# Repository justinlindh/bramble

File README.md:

<h1 align="center">Bramble</h1>

<p align="center">
  Privacy-first LoRa mesh networking for ESP32-S3, built with ESP-IDF.
</p>

<p align="center">

</p>

Bramble is an encrypted, multi-hop mesh protocol and firmware stack for long-range, infrastructure-free communication. It is designed for resilient field use while reducing metadata exposure; [docs/SECURITY-MODEL.md](docs/SECURITY-MODEL.md) documents exactly what is and is not protected.

## Table of Contents

- [What is Bramble?](#what-is-bramble)
- [What Makes Bramble Different](#what-makes-bramble-different)
- [Web Client](#web-client)
- [Hardware Targets](#hardware-targets)
- [Simulator](#simulator)
- [Emulator](#emulator)
- [Getting Started](#getting-started)
- [Testing](#testing)
- [Architecture](#architecture)
- [Documentation](#documentation)
- [API and SDK](#api-and-sdk)
- [CI/CD](#cicd)
- [Status](#status)
- [Contributing and Community](#contributing-and-community)
- [License](#license)

## What is Bramble?

Bramble is a secure LoRa mesh protocol and firmware implementation for ESP32-S3 devices with SX1262 radios. It focuses on practical private communications in constrained, lossy RF environments, with explicit handling for routing, retransmission, airtime limits, and node identity.

The firmware runs on real hardware (including T-Deck Plus and Heltec V3/V4 targets), with host-side testing used to validate protocol behavior continuously during development.

## What Makes Bramble Different

Compared to Meshtastic and MeshCore-style systems, Bramble leans on privacy and on authenticated, confirmable delivery at the protocol level. It is an early project: functional and hardware-verified on a small bench mesh, but not yet field-tested at scale. The claims below are what the code on `main` does, with the honest limits stated alongside.

- **Dual-substrate routing.** Two forwarding substrates ship, and a runtime toggle (`s_flood_transport`, default off) selects between them. **Reactive AODV is the default:** RREQ/RREP discovery, a cached route table, reverse-route breadcrumbs learned from DATA, intermediate-node RREP, and route-forwarded ACKs. DM airtime is `O(path_length)`, not `O(N)`. **Flooding is the opt-in alternative:** hop-limited (configurable, default 8, range 1..32), deduplicated, airtime-budget-gated unicast/channel floods with a flooded ACK for route-free sender confirmation. Both substrates are first-class; the toggle picks one.
- **Authenticated traffic (wire v4), no insecure bootstrap.** DATA frames and the control plane (RREP, RERR, ACK, delivery receipt, beacon) carry a network-key HMAC that relays verify before acting; a captured frame cannot be forged or replayed by an outsider on a provisioned network. There is no public default key: an unprovisioned node is inert (fail-closed) and refuses to emit or accept any authenticated frame until a real per-fleet key is provisioned (minted on-device or pasted in). Residual: any network-key holder is an insider and can still forge these MACs, narrowed by per-node identity rather than by provisioning ([docs/SECURITY-MODEL.md](docs/SECURITY-MODEL.md)).
- **Confirmed delivery.** Acknowledged tiers report DELIVERED vs FAILED to the sender rather than fire-and-forget. Honest envelope: reactive holds confirmed delivery at small, dense scale; the flooded confirmation holds at low-to-moderate message load and **degrades at high load** because flood airtime scales as `O(messages x nodes)`. It is explicitly not a high-load guarantee.
- **End-to-end direct messages.** DMs use per-peer AES-256-GCM sessions keyed by a role-symmetric quad-DH X25519 exchange (`components/dm_session`), and are not readable by other channel members. Each message has forward secrecy from a symmetric HKDF ratchet, with a coarse per-epoch DH ratchet for post-compromise recovery. An identity-bound 7-digit safety number (SAS) lets two people verify a contact out of band; the verification UX ships in the web client, the T-Deck graphical build, and on the e-paper pager itself (a per-peer view under the Nodes screen with a two-step confirm), and verified state is remembered per contact and cleared automatically if a contact's identity key changes. See [docs/SECURITY-MODEL.md](docs/SECURITY-MODEL.md) for the threat model and residuals.
- **Channel encryption + multi-hop channels.** Channel messages use AES-256-GCM (AEAD) with the channel ID hidden inside the ciphertext, and they relay multi-hop via the flood relay.
- **Privacy-first routing.** Route-request sources are pseudonymized per query, so forwarded route requests do not carry the originator's address.
- **Airtime budgeting:** every transmission goes through one budget-gated TX path (`components/radio/tx_gate.c`) with real time-on-air costing, per-tier token buckets, and regional duty-cycle caps enforced where the frequency plan requires them (for example EU 868 at 1%).
- **3-tier reliability model:** Broadcast (fire-and-forget), Normal (acknowledged, 3 retries with backoff), and Critical (8 retries plus delivery receipts carrying the relay path).
- **Cryptographic node identity + optional fleet trust anchor.** Each node has an Ed25519 identity whose 4-byte address is the hash of its own public key (`SHA-256(ed25519_pub)[0:4]`), so an address cannot be claimed without the matching key: address impersonation is a preimage search, not a TOFU race. Nodes flood self-signed identity attestations that peers verify and TOFU-pin, refusing and counting any later conflicting key for a pinned address. An optional per-fleet trust anchor (an operator-held Ed25519 key that endorses each member's identity with a cert) closes Sybil identity minting on an anchored mesh, because an anchored node only pins peers carrying a cert its anchor signed. Residuals stated in the same breath: a compromised endorsed insider stays a valid member (endorsement is admission control, not behavioral trust), the anchor seed is the fleet's trust root and its custody is the whole scheme, and an un-anchored mesh keeps unforgeable but free-to-mint identities ([docs/trust-anchor.md](docs/trust-anchor.md), [docs/SECURITY-MODEL.md](docs/SECURITY-MODEL.md)).
- **Attested roll-call.** An initiator broadcasts a roll-call and every member answers with an Ed25519 identity-signed unicast, building a per-member ledger with relay paths (`bramble.startRollCall` / `bramble.getRollCall`, with a panel in the web client). An anchored mesh audits against the endorsed member set; an un-anchored mesh reports observed responders only. A signature proves an answer and absence proves nothing; both initiation and answering are rate-limited because a roll-call costs N unicast answers. Verified by host tests and the collision-modeled simulator; no field deployment ([docs/rollcall.md](docs/rollcall.md)).
- **Deployment digital twin.** Each node exports its observed topology over RPC (`bramble.exportTopology`), and the simulator's `twin` subcommand replays that deployment against the collision model: capacity (delivery rate vs offered load) and which single node's loss partitions the mesh. The twin replays observed links at a moment in time; it predicts nothing about unplaced nodes, and its results are simulation ([docs/digital-twin.md](docs/digital-twin.md)).
- **Browser playground.** `make playground` boots the actual firmware binary as a small virtual fleet on a simulated ether, with a guided tour through provisioning (including the fail-closed inert state), multi-hop relay, SAS verification, and a delivery receipt. First contact needs no hardware and no toolchain; a browser fleet is not a field deployment ([docs/playground.md](docs/playground.md)).
- **Store-and-forward mailbox:** offline nodes receive queued messages when they rejoin the mesh.
- **Location sharing with privacy tiers:** presence, zone (a 0.003° by 0.006° cell, about 334 m north-south and 668 m east-west at the equator), or exact; per-peer control over what you share and with whom. Location payloads are AES-256-GCM encrypted end to end and padded to a fixed size so the ciphertext does not leak which tier was chosen; timing and the fact that a node shares location remain observable ([docs/SECURITY-MODEL.md](docs/SECURITY-MODEL.md)).
- **Browser-based flashing:** flash firmware to new devices directly from the web, no toolchain required.

For a deeper feature-by-feature analysis, see [docs/COMPARISON.md](docs/COMPARISON.md).

## Web Client

Bramble includes a web client for live network operation and monitoring. It provides real-time chat (including delivery badges), map-based peer location views, neighbor and route visualization, traffic monitoring, channel management, and radio configuration.

See [docs/webapp/chat.md](docs/webapp/chat.md) for current web client behavior and usage notes. To run it from source, `cd webapp && npm ci && npm run dev`; [webapp/README.md](webapp/README.md) covers the dev workflow, the WiFi-transport backend, and the Electron builds.

A desktop app (Linux, Windows, macOS) is also available, built from the same webapp. It connects directly to nodes on your local network instead of going through a hosted proxy, and can discover nodes on the LAN automatically. See [docs/webapp/desktop.md](docs/webapp/desktop.md).

## Hardware Targets

| Board | MCU | Display | Input | Radio | Audio | Status |
| ------ | ----- | --------- | ------- | ------- | ------- | -------- |
| Heltec WiFi LoRa 32 V3 | ESP32-S3 | 0.96" SSD1306 OLED (128x64) | Buttons | SX1262 | N/A | Running target |
| Heltec WiFi LoRa 32 V4 | ESP32-S3 | OLED + optional L76K GNSS | Buttons | SX1262 | N/A | Running target |
| LilyGo T-Deck Plus | ESP32-S3 | ST7789 320x240 LCD with LVGL v9 UI | GT911 capacitive touch + I2C keyboard | SX1262 with TCXO (DIO3 1.8V, DC-DC) | I2S with NVS-persisted volume | Running target with full GUI |
| Bramble Pager v1 (custom PCB) | ESP32-S3-WROOM-1 | 2.13" GDEY0213B74 e-paper (SSD1680, 250x122) | Buttons | SX1262 with TCXO and DIO2 RF switch (DC-DC) | Buzzer + vibra alerts | Design complete, boards not yet ordered |
| Seeed Wio-WM1110 Dev Kit | nRF52840 | None (BLE-only interface) | None | LR1110 | N/A | Experimental: joins the bench mesh, BLE RPC + provisioning over an encrypted link, identity/key/bonds persist in flash; GNSS and power management not yet implemented ([nrf/](nrf/)) |
| Seeed SenseCAP T1000-E (card tracker) | nRF52840 | None (BLE-only interface) | Button | LR1110 | Buzzer | Experimental: boots, BLE RPC, joins the mesh; GNSS driver implemented for the onboard AG3335 module and bench-verified (2026-07-31); power management not yet implemented ([nrf/](nrf/)) |

The Bramble Pager v1 is a custom in-house board, not an off-the-shelf dev kit: its own 96x50mm 2-layer PCB (ESP32-S3-WROOM-1 + SX1262 with a DIO2 RF switch, GDEY0213B74 2.13" e-paper, ATGM336H GPS, buzzer, vibration motor, and status LED), JLCPCB-fabbable, in a 3D-printed case. The authoritative design tree (spec, schematic, PCB, BOM, case, and bring-up gates) is [hardware/pager/v1/](hardware/pager/v1/); build it with the `bramble-pager` board profile.

This is what the firmware paints on each display class, as real framebuffers (T-Deck captured on hardware, the others rendered by the real firmware in the emulator):

<table>
<tr>
<td align="center" width="34%"></td>
<td align="center" width="33%"></td>
<td align="center" width="33%"></td>
</tr>
<tr>
<td align="center"><b>T-Deck Plus</b>: LVGL color UI</td>
<td align="center"><b>Heltec OLED</b>: text UI</td>
<td align="center"><b>Pager v1</b> (alpha): e-paper text UI</td>
</tr>
</table>

Each image links to its device's section in the [device screen gallery](docs/device-screens.md), which shows every screen and documents how each capture was made.

## Simulator

Bramble ships with a mesh simulator that runs real protocol code against a virtual radio layer and renders topology/traffic in a browser. The radio layer models the shared LoRa medium (real time-on-air, collisions, capture, half-duplex, listen-before-talk), making it the primary proving ground for scale and routing behavior before field deployment.

See [simulator/README.md](simulator/README.md) for setup and scenarios. For measured scale results under the collision model, [docs/results/simulation-2026-07-honest-baseline.md](docs/results/simulation-2026-07-honest-baseline.md) is the source of truth (it supersedes the June numbers for planning; the earlier collision-free "100% at 200 nodes" figures were retracted as sim artifacts). In short, re-measured on 2026-07-24 at the PHY firmware actually transmits on (the frequency plan's SF9/125 kHz, not the radio profile's SF10): 30% message delivery at 10 nodes, 10% at 50, 0-5% at 100 and 0% at 200, as a single channel saturates under control-plane load (0.91 erlang offered by control traffic alone at 50 nodes, 1.94 at 200). Scale is bounded by radio profile, node density, and hop budget; there is no field-tested-at-scale result.

## Emulator

The simulator drives real protocol code through a test harness; the emulator goes one step further and runs the **actual firmware binary**. Each virtual node is `app_main` compiled for ESP-IDF's linux target, booted with a virtual board profile, with the radio, e-paper display, buttons, GPS, and battery replaced by virtual drivers at the existing hardware seams. N virtual Bramble Pagers attach to the gosim ether and are rendered in a browser as the physical device: a faithful SSD1680 e-paper panel, clickable buttons, per-node consoles, and true per-node identities that survive restart. It is the packaging/UX proving ground the simulator is not: what a user actually sees and does on the device.

Quick start: `cd emulator && make run` (local toolchain) or `docker compose up --build` (zero prerequisites), then open the printed URL and load the `emu-channel-delivery` scenario. A gated PHY-passthrough bridge lets a serial-attached real node inject the physical RF channel into the virtual ether. See [emulator/README.md](emulator/README.md) for setup, scenarios, and the headless CI/E2E suites. A QEMU true-VM backend (running the exact flashable image) is a documented phase-2 follow-on, not yet built.

## Getting Started

Full build/flash instructions (including board-specific profiles and USB-port notes) are in [docs/BUILDING.md](docs/BUILDING.md).

Quick start (building from source needs ESP-IDF v5.4.1; see
[docs/BUILDING.md](docs/BUILDING.md) to install and activate it):

```bash
git clone https://github.com/justinlindh/bramble.git
cd bramble

# activate ESP-IDF in this shell first
source "$IDF_PATH/export.sh"

bash scripts/flash.sh local heltec-v3 build
bash scripts/flash.sh local heltec-v3 flash /dev/ttyUSB0
```

Use `tdeck-plus` instead of `heltec-v3` for T-Deck Plus builds.

No toolchain, no problem: the [web flasher](https://bramblemesh.org/web-flasher/)
flashes a device over USB straight from the browser. If a build or flash
stalls (serial permissions, a missing toolchain, a port collision), see
[docs/troubleshooting.md](docs/troubleshooting.md).

**Keeping it up to date.** Once a node is on your WiFi it installs new firmware over the air from the web client, no cable and no toolchain: [docs/updating-your-node.md](docs/updating-your-node.md).

**First-time setup.** A freshly flashed node boots unprovisioned and inert: it has no network key, so it will not mesh (it neither emits nor accepts authenticated control-plane traffic) until you provision one, and the web client shows a prominent UNPROVISIONED banner until then. Follow [docs/getting-started.md](docs/getting-started.md) to connect the web client, provision a network key, optionally enroll the node under a trust anchor, and send your first message.

## Testing

Host-side tests cover crypto, routing, security, packet handling, reliability, and integration behavior.

```bash
cd test
./run_all_tests.sh
```

## Architecture

Bramble is organized as ESP-IDF components with clear boundaries between protocol logic, radio abstraction, security, reliability, and UI/control layers. The architecture is designed so core protocol behavior can be validated on host and simulator environments before device rollout.

For the full component breakdown and interaction diagrams, see [docs/bramble-architecture.md](docs/bramble-architecture.md).

## Documentation

- [docs/README.md](docs/README.md): documentation index (recommended entry point)
- [CONTRIBUTING.md](CONTRIBUTING.md): contributor setup, quality gates, and conventions
- [docs/troubleshooting.md](docs/troubleshooting.md): common build, flash, and test stalls
- [docs/BUILDING.md](docs/BUILDING.md): build, flash, monitor workflows
- [docs/bramble-architecture.md](docs/bramble-architecture.md): component-level architecture
- [docs/SECURITY-MODEL.md](docs/SECURITY-MODEL.md): threat model, verified protections, and known gaps
- [docs/auth.md](docs/auth.md): RPC authentication (on by default), pairing, and the browser origin allowlist
- [docs/COMPARISON.md](docs/COMPARISON.md): comparison with other mesh systems
- [docs/bramble-protocol-spec.md](docs/bramble-protocol-spec.md): protocol details
- [docs/bramble-testing.md](docs/bramble-testing.md): test strategy and coverage
- [docs/updating-your-node.md](docs/updating-your-node.md): update your node over the air from the web client
- [docs/ota-rollout.md](docs/ota-rollout.md): OTA operator workflow (RPC recipes, dev-build loop)
- [docs/quality-policy.md](docs/quality-policy.md): repo-wide CI gates, promotion criteria, and rollback levers
- [docs/quality-policy-webapp.md](docs/quality-policy-webapp.md): webapp workflow required/advisory mapping, local parity commands, and rollback levers
- [simulator/README.md](simulator/README.md): simulator usage
- [docs/webapp/chat.md](docs/webapp/chat.md): web client chat and UX notes

## API and SDK

Bramble exposes a JSON-RPC 2.0 interface for device control and observability.

- [api/openapi.yaml](api/openapi.yaml): OpenAPI spec for the RPC surface (synced to the firmware registry, CI-enforced by `scripts/check-rpc-contract.sh`; see [VERSIONING.md](VERSIONING.md))
- [bramble-go](https://github.com/justinlindh/bramble-go): Go SDK (serial, WebSocket, BLE)
- [bramble-cli](https://github.com/justinlindh/bramble-cli): CLI/TUI built on bramble-go
- [VERSIONING.md](VERSIONING.md): compatibility matrix

## CI/CD

- [.github/workflows/quality.yml](.github/workflows/quality.yml) runs the umbrella required gates: host tests, static checks, gosim integration, webapp checks, web-flasher tests, and the emulator suite.
- [.github/workflows/firmware-quality.yml](.github/workflows/firmware-quality.yml) runs firmware quality gates: required clang-format/shellcheck/actionlint.
- [.github/workflows/webapp-quality.yml](.github/workflows/webapp-quality.yml) runs webapp required gates (lint/typecheck/unit/build/e2e smoke).
- [.github/workflows/release-components.yml](.github/workflows/release-components.yml) publishes per-component releases and attaches firmware factory images and desktop installers.
- Additional workflow definitions live in [.github/workflows](.github/workflows).

## Status

Bramble is an early but fully functional project: the protocol stack is implemented end to end, reviewed and host-tested, and running stable on real hardware (T-Deck Plus, Heltec V3, and Heltec V4). Every change must pass the full host test suite as a required CI gate (`test/run_all_tests.sh`, which fails if any suite fails or none are found). It has not yet been field-tested at scale, and development is ongoing.

## Contributing and Community

Contributions are welcome, and you do not need hardware to make one. The
webapp, the simulator, the host test suites, and the docs all build and run on
an ordinary machine.

- **[CONTRIBUTING.md](CONTRIBUTING.md)**: setup, the quality gates, branch and
  commit conventions, and what a good pull request looks like. Start there.
  Note the one step that is easy to miss: run `make setup-hooks` once per
  clone so the pre-commit checks run on your machine instead of failing in CI.
- **[docs/troubleshooting.md](docs/troubleshooting.md)**: serial permissions,
  toolchain targets, port collisions, and the other common first-run stalls.
- **[Issues](https://github.com/justinlindh/bramble/issues)**: bug reports and
  feature requests.
- **[Discussions](https://github.com/justinlindh/bramble/discussions)**:
  questions, ideas, and show-and-tell.
- **[SECURITY.md](SECURITY.md)**: how to report a vulnerability privately.
  Please do not open a public issue for one.
- **[CODE_OF_CONDUCT.md](CODE_OF_CONDUCT.md)**: what is expected of everyone
  taking part.

GitHub is canonical for outside contributions. Any other remote you may come
across is a mirror.

## License

MIT; see [LICENSE](LICENSE)

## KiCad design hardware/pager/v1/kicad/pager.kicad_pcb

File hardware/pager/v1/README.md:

# Bramble Pager v1

A full Bramble mesh node (TX-capable; the mesh has no receive-only role) built into a
90s-pager formfactor: always-readable 2.13" e-paper, 1S LiPo with USB-C charge and
load-share, magnetic buzzer plus coin vibration motor, and a 3D-printed enclosure. It
runs stock Bramble firmware as a new board target (`bramble_pager`) that reuses every
Heltec-V3 pin assignment legal on an ESP32-S3-WROOM-1, adds an SSD1680 e-paper display,
and carries an ATGM336H GNSS receiver. Board is ~96x50mm landscape, 2-layer 1.6mm,
built for JLCPCB economic PCBA. This directory is the source of truth for the design.

**Status:** design complete and merged to `main` (schematic, PCB, BOM, and enclosure done;
firmware board profile `main/boards/bramble_pager.h` landed). Boards are **not yet ordered**:
the pre-fab gates in [`ERRATA.md`](ERRATA.md) (FPC 1:1 fold mockup, bench-verified 0x9D
DIO2 RF-switch flag, final DRC 0/0/0) must close first. See
[the archived pre-fab review](../../../docs/archive/plans/pager-v1-review-2026-07-10.md)
for the independent pre-fab review and [`SOURCING.md`](SOURCING.md) for the hand-purchased
(non-JLCPCB) parts. Production outputs (gerbers, BOM, positions) are under
[`kicad/production/`](kicad/production/).

The full requirement set, pin map, block-by-block rationale, and firmware deltas live in
`DESIGN.md`. This README covers the workflow: where truth lives, how to validate, what
must never regress, and how to bring a first article up.

## Sources of truth (ranked)

When two artefacts disagree, the higher entry wins. Never argue with ERC or DRC; fix the
schematic or the doc.

| Rank | Artefact | Authority |
| --- | --- | --- |
| 1 | `kicad/*.kicad_sch` | Canonical electrical netlist. If a doc says a pin is wired to X and the schematic says Y, the schematic is correct. |
| 2 | `kicad/pager.kicad_pcb` | Canonical physical placement and routing. Authoritative for positions, layers, copper geometry. |
| 3 | `DESIGN.md` | Requirements, pin map, block rationale, do-not-regress invariants. |
| 4 | `COMPONENTS.md` | Per-component catalogue: value, package, LCSC part, nets, purpose, datasheet pinout citation. |
| 5 | `NET_TOPOLOGY.md` | Net-by-net prose for the nets that matter: why each exists, how each block is wired. |

`COMPONENTS.md` and `NET_TOPOLOGY.md` are derived docs. They mirror the schematic; if
either disagrees with a `.kicad_sch`, the schematic is right and the doc is a bug.

## File map

```text
hardware/pager/v1/
├── README.md            # this file
├── DESIGN.md            # authoritative spec: requirements, pin map, blocks, invariants
├── COMPONENTS.md        # per-component catalogue (derived)
├── NET_TOPOLOGY.md      # net-by-net wiring prose (derived)
├── ERRATA.md            # errata + pre-fab open items
├── SOURCING.md          # hand-purchased (non-JLCPCB) parts + live sources
├── mockup-fpc-1to1.pdf  # 1:1 FPC fold mockup (print gate before ordering)
├── case/                # OpenSCAD enclosure + exported STLs
└── kicad/
    ├── pager.kicad_pro  # KiCad project
    ├── pager.kicad_sch  # root sheet (hierarchical references only)
    ├── power.kicad_sch  # USB-C, charger, protection, load-share, LDO
    ├── radio.kicad_sch  # LoRa module, GNSS module, both RF feeds
    ├── epaper.kicad_sch # display connector + boost / charge-pump
    ├── mcu.kicad_sch    # ESP32-S3, buttons, buzzer, vibra, LED, I2C header
    ├── pager.kicad_pcb  # PCB layout
    ├── pager.kicad_dru  # hard DRC backstops (RF, power-rail widths)
    ├── production/      # fabrication outputs: gerbers, bom.csv, positions
    └── easyeda/         # imported footprints/symbols (dimension-verified)
```

The original implementation plan and the independent pre-fab review are historical
process artifacts and live under [`docs/archive/plans/`](../../../docs/archive/plans/):
[`pager-v1-plan.md`](../../../docs/archive/plans/pager-v1-plan.md) and
[`pager-v1-review-2026-07-10.md`](../../../docs/archive/plans/pager-v1-review-2026-07-10.md).

## Validation gates

Both gates use `kicad-cli` (not the KiCad MCP). MCP ERC/DRC read stale in-memory state
and have missed real violations; they are never authoritative here.

### Schematic ERC

```bash
kicad-cli sch erc --severity-error --exit-code-violations \
  hardware/pager/v1/kicad/pager.kicad_sch -o /tmp/erc.rpt
```

Must exit 0 (zero errors). The committed `kicad/pager-erc.rpt` is the last clean run.

### PCB DRC

```bash
kicad-cli pcb drc --refill-zones \
  hardware/pager/v1/kicad/pager.kicad_pcb -o /tmp/drc.rpt
```

Must report 0 unconnected, 0 clearance, 0 dangling. `--refill-zones` is mandatory;
without it DRC reads stale zone fills and misses zone-island and same-layer clearance
violations. The `.kicad_dru` net-name patterns must be re-audited against the actual
hierarchical net names (`/sheet/NET`) before every fab; a pattern that silently voids
against a renamed net gives a false-clean pass (the Digits v2 SW_NODE lesson).

## Do-not-regress invariants

Copied from `DESIGN.md`. Regressing any of these is a production defect.

- Every non-stdlib pinout and every pin-numbering orientation must be verified against
  the manufacturer datasheet (page/figure cited in `COMPONENTS.md`). EasyEDA part data,
  vendor symbol drawings, and "it is usually like this" do NOT count as verification.
  Claims that could not be datasheet-confirmed are tracked as open risks, not assumed.
- CC1 and CC2 each get their own 5.1k, never shared.
- Battery sense divider taps BAT+ (cell side), not VSYS.
- RESE resistor is 2.2 ohm 1% 0805 with kelvin sense to panel pin 3.
- EPD connector netlist is mirrored (connector N = panel 25-N); paper-mockup gate
  before gerbers.
- Parts under the panel deck rect stay <=3.2mm tall; the deck carries the glass 6mm
  above the PCB (raised from 4mm so the mated LoRa u.FL under the panel clears the module
  underside). The enclosure module-pocket interference check (SCAD asserts + rendered
  previews) is the physical gate, superseding the old 1mm glass keepout.
- RF trace: CPW, <5mm, stitched ground, no crossings; u.FL at case-wall edge.
- WROOM antenna keepout all layers.
- TCXO voltage 2.7V for this module (not 1.7V).
- 0x9D firmware flag lands + is bench-verified before boards are ordered.
- Netclass patterns audited against hierarchical net names (`/sheet/NET`) before fab.
- Gates: `kicad-cli sch erc --severity-error --exit-code-violations` = 0;
  `kicad-cli pcb drc --refill-zones` = 0/0/0 (never MCP ERC/DRC).

## Bring-up checklist

Order matters. Do not order boards until the pre-fab gates (below and in `ERRATA.md`)
are closed.

Before gerbers:

1. **FPC 1:1 paper mockup gate.** Print the panel tail + 180-degree fold + FH34SRJ-24S
   connector at 1:1. Confirm the mirrored pin order physically lands (connector pin N to
   panel pin 25-N). The whole EPD netlist depends on this fold geometry being right.
2. **DIO2 RF-switch flag.** Confirm the `radio_dio2_rf_switch` firmware flag has landed
   and been bench-verified on a Heltec V3 A/B test. Without the one-time 0x9D
   (`SetDio2AsRfSwitchCtrl`, payload 0x01) this module's chip-internal RF switch never
   arms and TX is dead.
3. **WROOM antenna copper keepout.** Confirm there is no copper pour on any layer under
   the WROOM-1 PCB-antenna zone (the module pads start ~4mm inside the left board edge;
   the antenna sits on-board over the keepout, it does not overhang the edge).

At first-article bring-up:

1. **DMM battery polarity check on every cell before first plug.** BATT1 pin 1 = BAT+
   (Adafruit convention). Reversed Chinese cells kill the charger. This is a per-unit
   assembly invariant, not a one-time check.
2. **TCXO voltage verify.** The module's TCXO is 2.8V nominal; firmware sets the nearest
   SX1262 code, 2.7V. Confirm the radio brings up and TXs cleanly at 2.7V; if not, try
   3.0V. Bench against a known-good Heltec V3 for a reference RSSI.
3. **NMEA talker-ID check.** The ATGM336H is CASIC/AT6558 (GPS+BDS) and emits `$GN`/`$GB`
   talker IDs, not just `$GP`. Confirm the firmware NMEA parser accepts them, and that
   `$GPTXT` antenna OPEN/SHORT reporting reads sane against the active GNSS antenna.

## Firmware build

The pager target is already wired into `scripts/flash.sh`. From the firmware repo root:

```bash
bash scripts/flash.sh local bramble-pager build
```

This applies `sdkconfig.bramble-pager` +
`SDKCONFIG_DEFAULTS="sdkconfig.defaults;sdkconfig.defaults.bramble_pager"` into
`build-bramble-pager/`. The output image is `build-bramble-pager/bramble.bin`. Console is
USB-Serial-JTAG (`CONFIG_ESP_CONSOLE_USB_SERIAL_JTAG=y`), no UART bridge; flash and
monitor over the native USB-C. Board profile is `main/boards/bramble_pager.h`.

Equivalent direct `idf.py` form (use only for low-level control):

```bash
idf.py -B build-bramble-pager \
  -D SDKCONFIG=sdkconfig.bramble-pager \
  -D SDKCONFIG_DEFAULTS="sdkconfig.defaults;sdkconfig.defaults.bramble_pager" \
  build
```

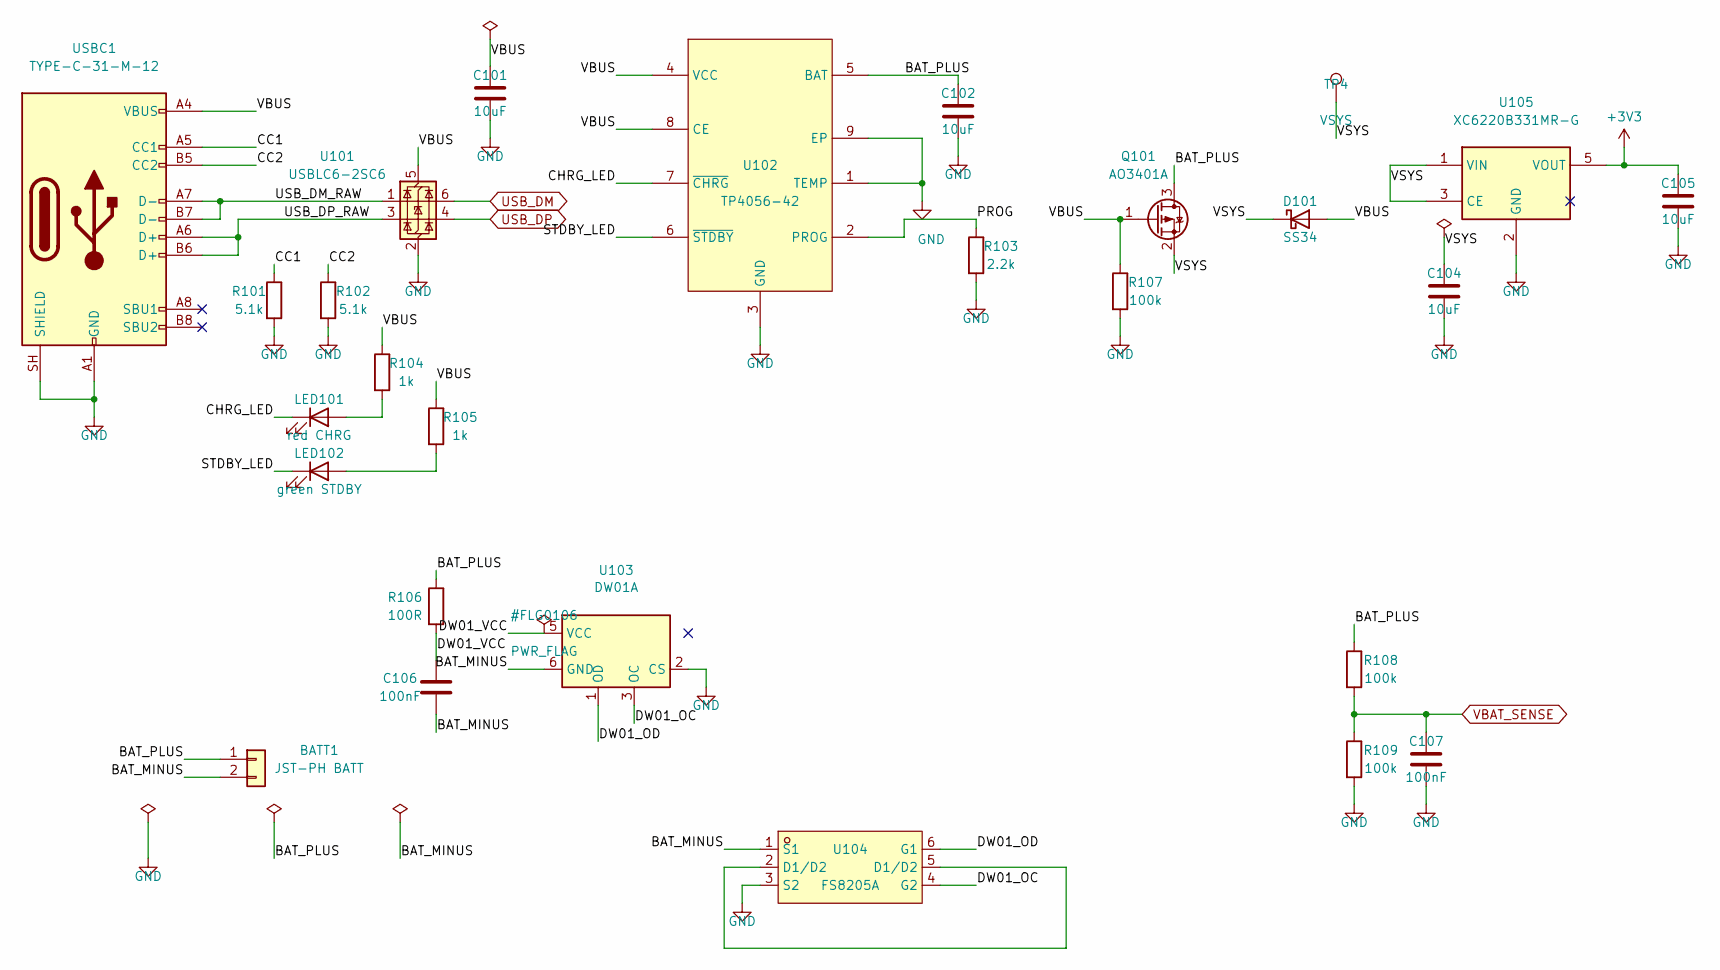
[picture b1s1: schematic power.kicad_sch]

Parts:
BATT1: JST-PH BATT; JST_PH_S2B-PH-SM4-TB_1x02-1MP_P2.00mm_Horizontal; LCSC C295747
C101, C102, C104, C105: 10uF; C_0805_2012Metric; LCSC C15850
C106, C107: 100nF; C_0603_1608Metric; LCSC C14663
D101: SS34; D_SMA; LCSC C8678
LED101: red CHRG; LED_0603_1608Metric; LCSC C2286
LED102: green STDBY; LED_0603_1608Metric; LCSC C965805
Q101: AO3401A; SOT-23; LCSC C15127
R101, R102: 5.1k; R_0603_1608Metric; LCSC C23186
R103: 2.2k; R_0603_1608Metric; LCSC C4190
R104, R105: 1k; R_0603_1608Metric; LCSC C21190
R106: 100R; R_0603_1608Metric; LCSC C22775
R107, R108, R109: 100k; R_0603_1608Metric; LCSC C25803
TP4: VSYS; TestPoint_Pad_1.5x1.5mm; LCSC DNP
U101: USBLC6-2SC6; SOT-23-6; LCSC C2687116
U102: TP4056-42; ESOP-8_L4.9-W3.9-P1.27-LS6.0-BL-EP; LCSC C16581
U103: DW01A; SOT-23-6; LCSC C351410
U104: FS8205A; SOT-23-6_L2.9-W1.6-P0.95-LS2.8-BR; LCSC C2830320
U105: XC6220B331MR-G; SOT-23-5; LCSC C86534
USBC1: TYPE-C-31-M-12; USB_C_Receptacle_HRO_TYPE-C-31-M-12; LCSC C165948

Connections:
+3V3: C105.1, U105.5 (VOUT); also elsewhere on the board
/power/BAT_MINUS: BATT1.2, C106.2, U103.6 (GND), U104.1 (S1)
/power/BAT_PLUS: BATT1.1, C102.1, Q101.3 (D), R106.1, R108.1, U102.5 (BAT)
/power/CC1: R101.1, USBC1.A5 (CC1)
/power/CC2: R102.1, USBC1.B5 (CC2)
/power/CHRG_LED: LED101.1 (K), U102.7 (~CHRG)
/power/DW01_OC: U103.3 (OC), U104.4 (G2)
/power/DW01_OD: U103.1 (OD), U104.6 (G1)
/power/DW01_VCC: C106.1, R106.2, U103.5 (VCC)
/power/PROG: R103.1, U102.2 (PROG)
/power/STDBY_LED: LED102.1 (K), U102.6 (~STDBY)
/power/USB_DM_RAW: U101.1 (I/O1), USBC1.A7 (D-), USBC1.B7 (D-)
/power/USB_DP_RAW: U101.3 (I/O2), USBC1.A6 (D+), USBC1.B6 (D+)
/power/VBUS: C101.1, D101.2 (A), Q101.1 (G), R104.1, R105.1, R107.1, U101.5 (VBUS), U102.4 (VCC), U102.8 (CE), USBC1.A4 (VBUS), USBC1.A9 (VBUS), USBC1.B4 (VBUS), USBC1.B9 (VBUS)
/power/VSYS: C104.1, D101.1 (K), Q101.2 (S), TP4.1, U105.1 (VIN), U105.3 (CE)
GND: C101.2, C102.2, C104.2, C105.2, C107.2, R101.2, R102.2, R103.2, R107.2, R109.2, U101.2 (GND), U102.1 (TEMP), U102.3 (GND), U102.9 (EP), U103.2 (CS), U104.3 (S2), U105.2 (GND), USBC1.A1 (GND), USBC1.A12 (GND), USBC1.B1 (GND), USBC1.B12 (GND), USBC1.SH (SHIELD); also elsewhere on the board
unnamed: LED101.2 (A), R104.2
unnamed: LED102.2 (A), R105.2
unnamed: U104.2 (D1/D2), U104.5 (D1/D2)
USB_DM: U101.6 (I/O1); also elsewhere on the board
USB_DP: U101.4 (I/O2); also elsewhere on the board
VBAT_SENSE: C107.1, R108.2, R109.1; also elsewhere on the board

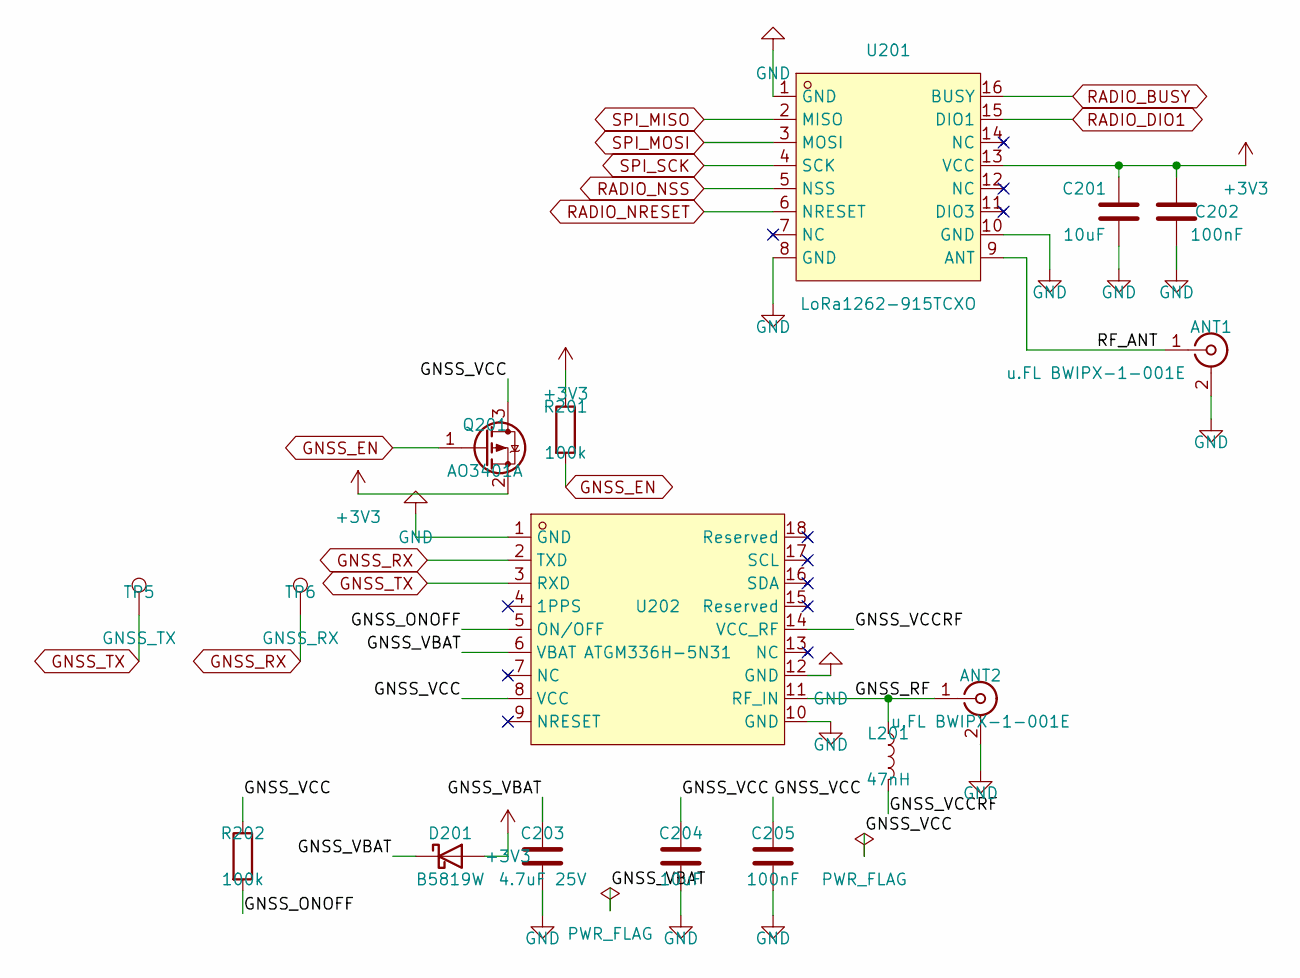
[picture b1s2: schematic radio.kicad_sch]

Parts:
ANT1, ANT2: u.FL BWIPX-1-001E; U.FL_Hirose_U.FL-R-SMT-1_Vertical; LCSC C496552
C201, C204: 10uF; C_0805_2012Metric; LCSC C15850
C202, C205: 100nF; C_0603_1608Metric; LCSC C14663
C203: 4.7uF 25V; C_0805_2012Metric; LCSC C1779
D201: B5819W; D_SOD-123; LCSC C8598
L201: 47nH; L_0402_1005Metric; LCSC C22334
Q201: AO3401A; SOT-23; LCSC C15127
R201, R202: 100k; R_0603_1608Metric; LCSC C25803
TP5: GNSS_TX; TestPoint_Pad_1.5x1.5mm; LCSC DNP
TP6: GNSS_RX; TestPoint_Pad_1.5x1.5mm; LCSC DNP
U201: LoRa1262-915TCXO; WIRELM-SMD_16P-L16.0-W16.0-P2.00_LORA-CC68-915MHZ-TCXO; LCSC C5356643
U202: ATGM336H-5N31; GPSM-SMD_ATGM336H-TR; LCSC C90770

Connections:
+3V3: C201.1, C202.1, D201.2 (A), Q201.2 (S), R201.1, U201.13 (VCC); also elsewhere on the board
/radio/GNSS_ONOFF: R202.2, U202.5 (ON/OFF)
/radio/GNSS_RF: ANT2.1 (In), L201.1, U202.11 (RF_IN)
/radio/GNSS_VBAT: C203.1, D201.1 (K), U202.6 (VBAT)
/radio/GNSS_VCC: C204.1, C205.1, Q201.3 (D), R202.1, U202.8 (VCC)
/radio/GNSS_VCCRF: L201.2, U202.14 (VCC_RF)
/radio/RF_ANT: ANT1.1 (In), U201.9 (ANT)
GND: ANT1.2 (Ext), ANT2.2 (Ext), C201.2, C202.2, C203.2, C204.2, C205.2, U201.1 (GND), U201.8 (GND), U201.10 (GND), U202.1 (GND), U202.10 (GND), U202.12 (GND); also elsewhere on the board
GNSS_EN: Q201.1 (G), R201.2; also elsewhere on the board
GNSS_RX: TP6.1, U202.2 (TXD); also elsewhere on the board
GNSS_TX: TP5.1, U202.3 (RXD); also elsewhere on the board
RADIO_BUSY: U201.16 (BUSY); also elsewhere on the board
RADIO_DIO1: U201.15 (DIO1); also elsewhere on the board
RADIO_NRESET: U201.6 (NRESET); also elsewhere on the board
RADIO_NSS: U201.5 (NSS); also elsewhere on the board
SPI_MISO: U201.2 (MISO); also elsewhere on the board
SPI_MOSI: U201.3 (MOSI); also elsewhere on the board
SPI_SCK: U201.4 (SCK); also elsewhere on the board

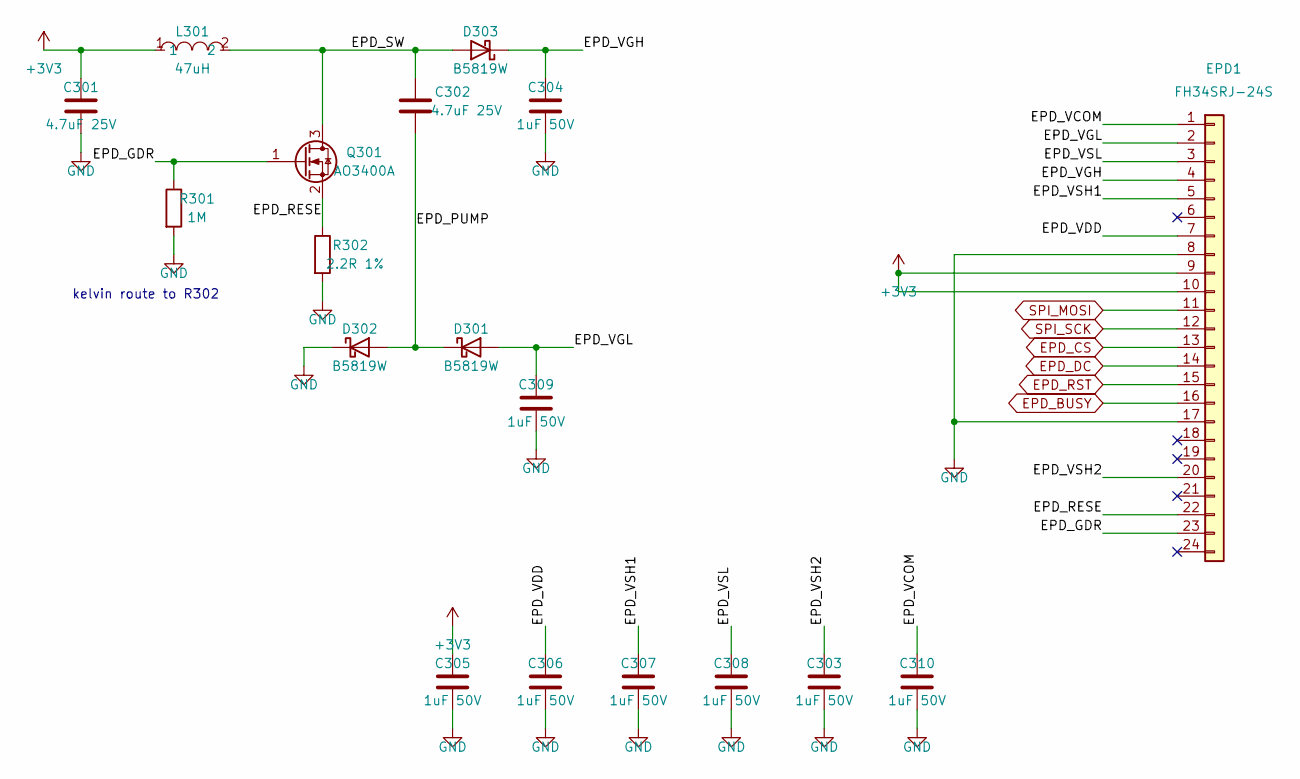
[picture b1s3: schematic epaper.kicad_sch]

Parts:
C301, C302: 4.7uF 25V; C_0805_2012Metric; LCSC C1779
C303, C304, C305, C306, C307, C308, C309, C310: 1uF 50V; C_0603_1608Metric; LCSC C15849
D301, D302, D303: B5819W; D_SOD-123; LCSC C8598
EPD1: FH34SRJ-24S; FFC-SMD_24P-P0.50_FH34SRJ-24S-0.5SH; LCSC C324726
L301: 47uH; IND-SMD_L4.0-W4.0_FNR40XXS; LCSC C167888
Q301: AO3400A; SOT-23; LCSC C20917
R301: 1M; R_0603_1608Metric; LCSC C22935
R302: 2.2R 1%; R_0805_2012Metric; LCSC C2933402

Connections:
+3V3: C301.1, C305.1, EPD1.9, EPD1.10, L301.1; also elsewhere on the board
/epaper/EPD_GDR: EPD1.23, Q301.1 (G), R301.1
/epaper/EPD_PUMP: C302.2, D301.1 (K), D302.2 (A)
/epaper/EPD_RESE: EPD1.22, Q301.2 (S), R302.1
/epaper/EPD_SW: C302.1, D303.2 (A), L301.2, Q301.3 (D)
/epaper/EPD_VCOM: C310.1, EPD1.1
/epaper/EPD_VDD: C306.1, EPD1.7
/epaper/EPD_VGH: C304.1, D303.1 (K), EPD1.4
/epaper/EPD_VGL: C309.1, D301.2 (A), EPD1.2
/epaper/EPD_VSH1: C307.1, EPD1.5
/epaper/EPD_VSH2: C303.1, EPD1.20
/epaper/EPD_VSL: C308.1, EPD1.3
EPD_BUSY: EPD1.16; also elsewhere on the board
EPD_CS: EPD1.13; also elsewhere on the board
EPD_DC: EPD1.14; also elsewhere on the board
EPD_RST: EPD1.15; also elsewhere on the board
GND: C301.2, C303.2, C304.2, C305.2, C306.2, C307.2, C308.2, C309.2, C310.2, D302.1 (K), EPD1.8, EPD1.17, R301.2, R302.2; also elsewhere on the board
SPI_MOSI: EPD1.11; also elsewhere on the board
SPI_SCK: EPD1.12; also elsewhere on the board

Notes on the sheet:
kelvin route to R302

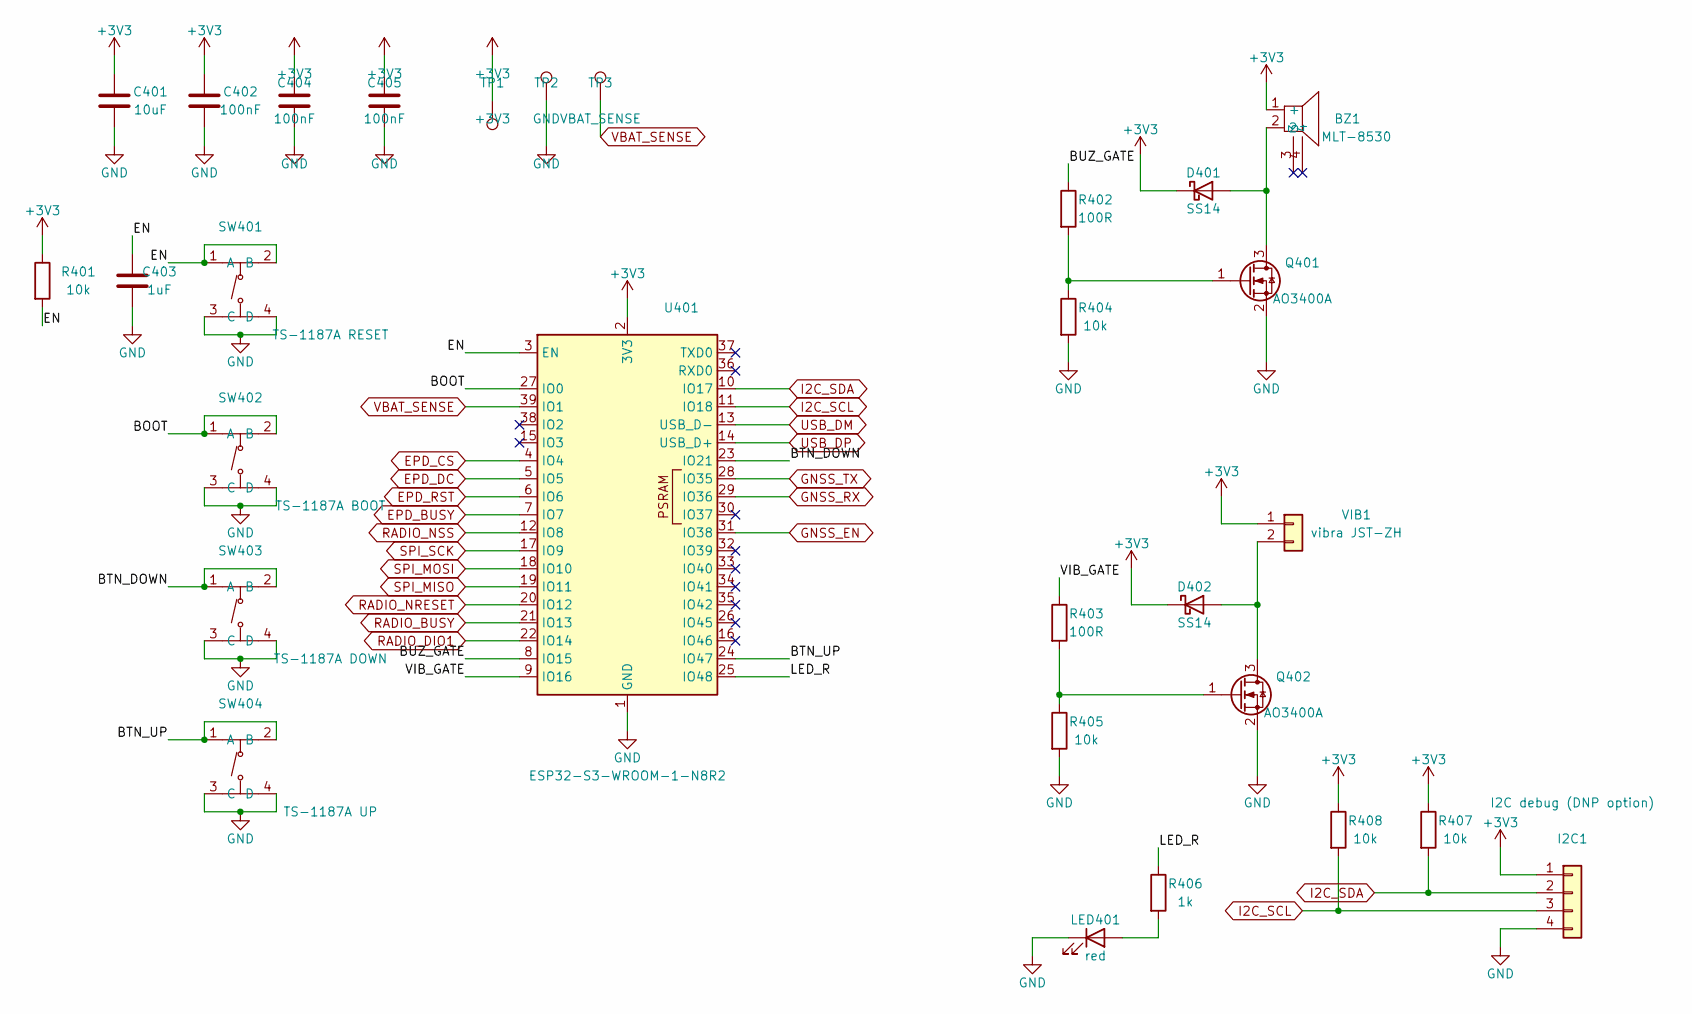
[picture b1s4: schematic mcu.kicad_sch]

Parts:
BZ1: MLT-8530; BUZ-SMD_4P-L8.5-W8.5-P8.50-BR; LCSC C94599
C401: 10uF; C_0805_2012Metric; LCSC C15850
C402: 100nF; C_0603_1608Metric; LCSC C14663
C403: 1uF; C_0603_1608Metric; LCSC C15849
C404, C405: 100nF; C_0603_1608Metric
D401, D402: SS14; D_SMA; LCSC C2480
I2C1: I2C debug (DNP option); JST_ZH_B4B-ZR-SM4-TF_1x04-1MP_P1.50mm_Vertical; LCSC C265083
LED401: red; LED_0603_1608Metric; LCSC C2286
Q401, Q402: AO3400A; SOT-23; LCSC C20917
R401, R404, R405, R407, R408: 10k; R_0603_1608Metric; LCSC C25804
R402, R403: 100R; R_0603_1608Metric; LCSC C22775
R406: 1k; R_0603_1608Metric; LCSC C21190
SW401: TS-1187A RESET; SW-SMD_4P-L5.1-W5.1-P3.70-LS6.5-TL_H1.5; LCSC C318884
SW402: TS-1187A BOOT; SW-SMD_4P-L5.1-W5.1-P3.70-LS6.5-TL_H1.5; LCSC C318884
SW403: TS-1187A DOWN; SW-SMD_4P-L5.1-W5.1-P3.70-LS6.5-TL_H1.5; LCSC C318884
SW404: TS-1187A UP; SW-SMD_4P-L5.1-W5.1-P3.70-LS6.5-TL_H1.5; LCSC C318884
TP1: +3V3; TestPoint_Pad_1.5x1.5mm; LCSC DNP
TP2: GND; TestPoint_Pad_1.5x1.5mm; LCSC DNP
TP3: VBAT_SENSE; TestPoint_Pad_1.5x1.5mm; LCSC DNP
U401: ESP32-S3-WROOM-1-N8R2; ESP32-S3-WROOM-1; LCSC C2913204
VIB1: vibra JST-ZH; JST_ZH_B2B-ZR-SM4-TF_1x02-1MP_P1.50mm_Vertical; LCSC C265284

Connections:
+3V3: BZ1.1 (+), C401.1, C402.1, C404.1, C405.1, D401.1 (K), D402.1 (K), I2C1.1, R401.1, R407.1, R408.1, TP1.1, U401.2 (3V3), VIB1.1; also elsewhere on the board
/mcu/BOOT: SW402.1 (A), SW402.2 (B), U401.27 (IO0)
/mcu/BTN_DOWN: SW403.1 (A), SW403.2 (B), U401.23 (IO21)
/mcu/BTN_UP: SW404.1 (A), SW404.2 (B), U401.24 (IO47)
/mcu/BUZ_GATE: R402.1, U401.8 (IO15)
/mcu/EN: C403.1, R401.2, SW401.1 (A), SW401.2 (B), U401.3 (EN)
/mcu/LED_R: R406.1, U401.25 (IO48)
/mcu/VIB_GATE: R403.1, U401.9 (IO16)
EPD_BUSY: U401.7 (IO7); also elsewhere on the board
EPD_CS: U401.4 (IO4); also elsewhere on the board
EPD_DC: U401.5 (IO5); also elsewhere on the board
EPD_RST: U401.6 (IO6); also elsewhere on the board
GND: C401.2, C402.2, C403.2, C404.2, C405.2, I2C1.4, LED401.1 (K), Q401.2 (S), Q402.2 (S), R404.2, R405.2, SW401.3 (C), SW401.4 (D), SW402.3 (C), SW402.4 (D), SW403.3 (C), SW403.4 (D), SW404.3 (C), SW404.4 (D), TP2.1, U401.1 (GND), U401.40 (GND), U401.41 (GND); also elsewhere on the board
GNSS_EN: U401.31 (IO38); also elsewhere on the board
GNSS_RX: U401.29 (IO36); also elsewhere on the board
GNSS_TX: U401.28 (IO35); also elsewhere on the board
I2C_SCL: I2C1.3, R408.2, U401.11 (IO18)
I2C_SDA: I2C1.2, R407.2, U401.10 (IO17)
unnamed: BZ1.2, D401.2 (A), Q401.3 (D)
unnamed: D402.2 (A), Q402.3 (D), VIB1.2
unnamed: LED401.2 (A), R406.2
unnamed: Q401.1 (G), R402.2, R404.1
unnamed: Q402.1 (G), R403.2, R405.1
RADIO_BUSY: U401.21 (IO13); also elsewhere on the board
RADIO_DIO1: U401.22 (IO14); also elsewhere on the board
RADIO_NRESET: U401.20 (IO12); also elsewhere on the board
RADIO_NSS: U401.12 (IO8); also elsewhere on the board
SPI_MISO: U401.19 (IO11); also elsewhere on the board
SPI_MOSI: U401.18 (IO10); also elsewhere on the board
SPI_SCK: U401.17 (IO9); also elsewhere on the board
USB_DM: U401.13 (USB_D-); also elsewhere on the board
USB_DP: U401.14 (USB_D+); also elsewhere on the board
VBAT_SENSE: TP3.1, U401.39 (IO1); also elsewhere on the board

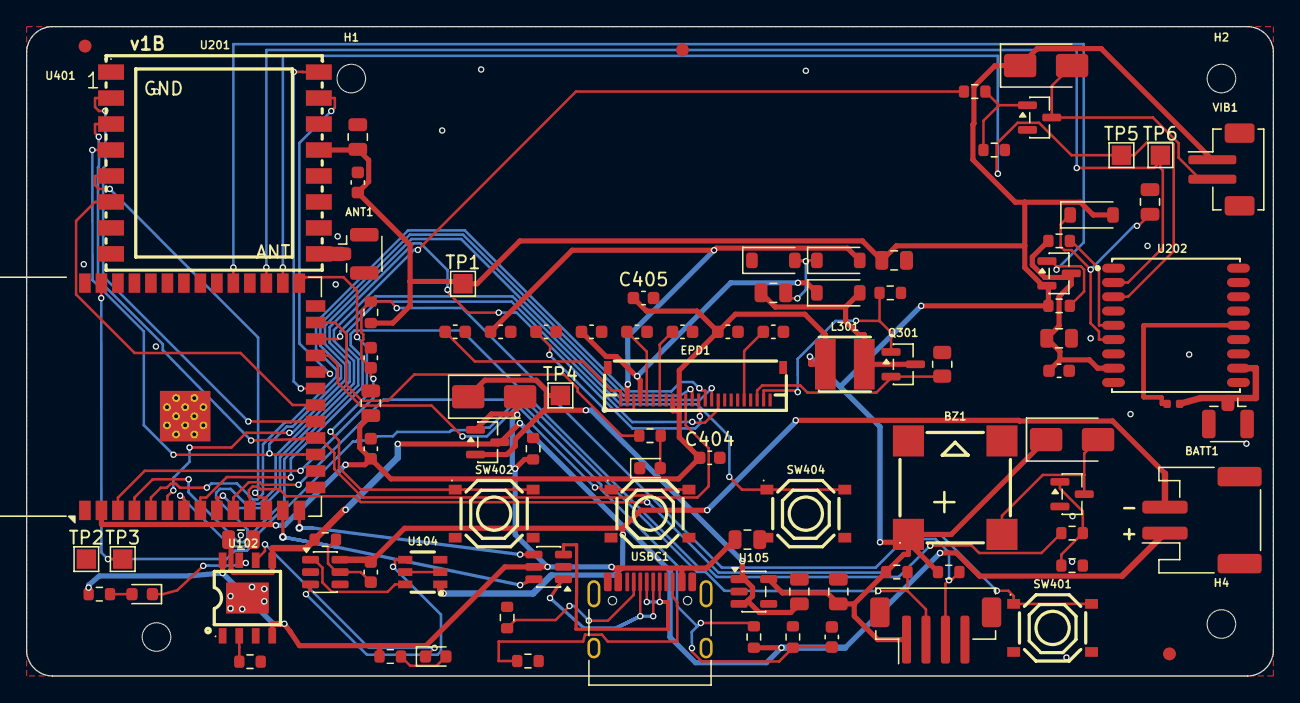
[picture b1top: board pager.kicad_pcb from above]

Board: 2 copper layers, 96.0 x 50.0 mm, 97 parts (0 on the bottom side), 67 nets.

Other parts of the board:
FID1, FID2, FID3: Fiducial; Fiducial_1mm_Mask3mm
H1, H2, H3, H4: MountingHole_2.2mm_M2

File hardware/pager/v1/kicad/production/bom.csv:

Comment,Designator,Footprint,LCSC Part #
100nF,"C106,C107,C202,C205,C402,C404,C405",C_0603_1608Metric,C14663
AO3401A,"Q101,Q201",SOT-23,C15127
1uF 50V,"C303,C304,C305,C306,C307,C308,C309,C310",C_0603_1608Metric,C15849
1uF,C403,C_0603_1608Metric,C15849
10uF,"C101,C102,C104,C105,C201,C204,C401",C_0805_2012Metric,C15850
TP4056-42,U102,ESOP-8_L4.9-W3.9-P1.27-LS6.0-BL-EP,C16581
TYPE-C-31-M-12,USBC1,USB_C_Receptacle_HRO_TYPE-C-31-M-12,C165948
47uH,L301,IND-SMD_L4.0-W4.0_FNR40XXS,C167888
4.7uF 25V,"C203,C301,C302",C_0805_2012Metric,C1779
AO3400A,"Q301,Q401,Q402",SOT-23,C20917
1k,"R104,R105,R406",R_0603_1608Metric,C21190
47nH,L201,L_0402_1005Metric,C22334
100R,"R106,R402,R403",R_0603_1608Metric,C22775
red CHRG,LED101,LED_0603_1608Metric,C2286
red,LED401,LED_0603_1608Metric,C2286
1M,R301,R_0603_1608Metric,C22935
5.1k,"R101,R102",R_0603_1608Metric,C23186
SS14,"D401,D402",D_SMA,C2480
100k,"R107,R108,R109,R201,R202",R_0603_1608Metric,C25803
10k,"R401,R404,R405,R407,R408",R_0603_1608Metric,C25804
I2C debug (DNP option),I2C1,JST_ZH_B4B-ZR-SM4-TF_1x04-1MP_P1.50mm_Vertical,C265083
vibra JST-ZH,VIB1,JST_ZH_B2B-ZR-SM4-TF_1x02-1MP_P1.50mm_Vertical,C265284
USBLC6-2SC6,U101,SOT-23-6,C2687116
FS8205A,U104,SOT-23-6_L2.9-W1.6-P0.95-LS2.8-BR,C2830320
ESP32-S3-WROOM-1-N8R2,U401,ESP32-S3-WROOM-1,C2913204
2.2R 1%,R302,R_0805_2012Metric,C2933402
JST-PH BATT,BATT1,JST_PH_S2B-PH-SM4-TB_1x02-1MP_P2.00mm_Horizontal,C295747
TS-1187A UP,SW404,SW-SMD_4P-L5.1-W5.1-P3.70-LS6.5-TL_H1.5,C318884
TS-1187A RESET,SW401,SW-SMD_4P-L5.1-W5.1-P3.70-LS6.5-TL_H1.5,C318884
TS-1187A DOWN,SW403,SW-SMD_4P-L5.1-W5.1-P3.70-LS6.5-TL_H1.5,C318884
TS-1187A BOOT,SW402,SW-SMD_4P-L5.1-W5.1-P3.70-LS6.5-TL_H1.5,C318884
FH34SRJ-24S,EPD1,FFC-SMD_24P-P0.50_FH34SRJ-24S-0.5SH,C324726
DW01A,U103,SOT-23-6,C351410
2.2k,R103,R_0603_1608Metric,C4190
u.FL BWIPX-1-001E,"ANT1,ANT2",U.FL_Hirose_U.FL-R-SMT-1_Vertical,C496552
LoRa1262-915TCXO,U201,WIRELM-SMD_16P-L16.0-W16.0-P2.00_LORA-CC68-915MHZ-TCXO,C5356643
B5819W,"D201,D301,D302,D303",D_SOD-123,C8598
XC6220B331MR-G,U105,SOT-23-5,C86534
SS34,D101,D_SMA,C8678
ATGM336H-5N31,U202,GPSM-SMD_ATGM336H-TR,C90770
MLT-8530,BZ1,BUZ-SMD_4P-L8.5-W8.5-P8.50-BR,C94599
green STDBY,LED102,LED_0603_1608Metric,C965805
